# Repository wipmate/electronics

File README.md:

# 📟 Electronics

A collection of small ESP32-powered PCBs for use in smart home appliances.

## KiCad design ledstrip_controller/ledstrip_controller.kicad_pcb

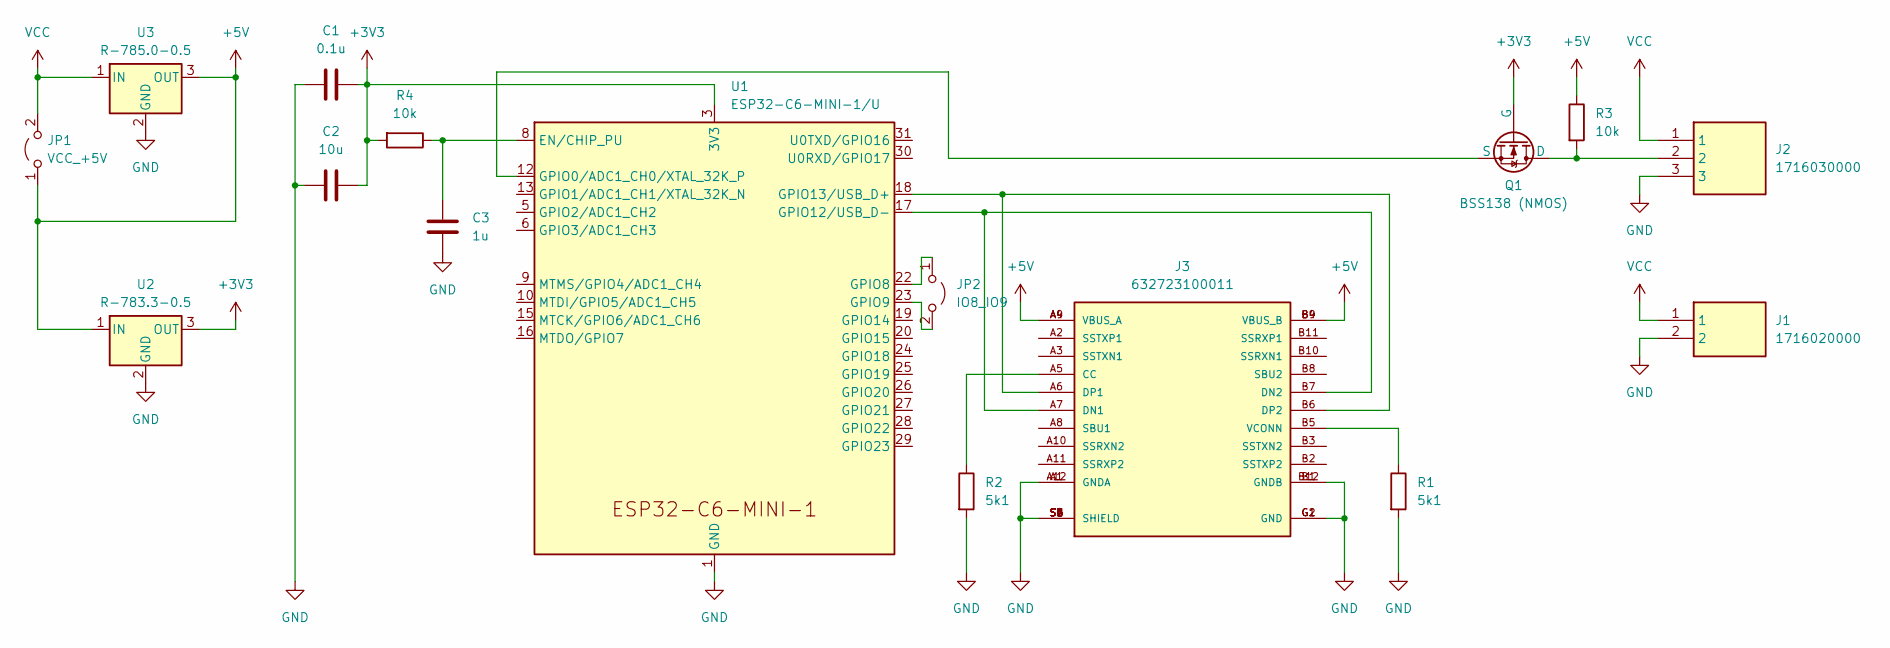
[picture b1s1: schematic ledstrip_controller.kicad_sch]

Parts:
C1: 0.1u; C_0603_1608Metric
C2: 10u; C_0603_1608Metric
C3: 1u; C_0603_1608Metric
J1: 1716020000; Mouser Part Number 470-1716020000
J2: 1716030000; Mouser Part Number 470-1716030000
J3: 632723100011; WURTH_632723100011; PARTREV 001.003
JP1: VCC_+5V; SolderJumper-2_P1.3mm_Open_Pad1.0x1.5mm
JP2: IO8_IO9; SolderJumper-2_P1.3mm_Open_Pad1.0x1.5mm
Q1: BSS138 (NMOS); SOT-23-3
R1, R2: 5k1; R_0603_1608Metric
R3, R4: 10k; R_0603_1608Metric
U1: ESP32-C6-MINI-1/U; ESP32-C6-MINI-1
U2: R-783.3-0.5; Converter_DCDC_RECOM_R-78E-0.5_THT
U3: R-785.0-0.5; Converter_DCDC_RECOM_R-78E-0.5_THT

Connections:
+3V3: C1.2, C2.2, Q1.2 (G), R4.2, U1.3 (3V3), U2.3 (OUT)
+5V: J3.A4 (VBUS_A), J3.A9 (VBUS_A), J3.B4 (VBUS_B), J3.B9 (VBUS_B), JP1.1 (A), R3.1, U2.1 (IN), U3.3 (OUT)
GND: C1.1, C2.1, C3.2, J1.2, J2.3, J3.A1 (GNDA), J3.A12 (GNDA), J3.B1 (GNDB), J3.B12 (GNDB), J3.G1 (GND), J3.G2 (GND), J3.S1 (SHIELD), J3.S2 (SHIELD), J3.S3 (SHIELD), J3.S4 (SHIELD), J3.S5 (SHIELD), J3.S6 (SHIELD), R1.2, R2.2, U1.1 (GND), U1.2 (GND), U1.11 (GND), U1.14 (GND), U1.36 (GND), U1.37 (GND), U1.38 (GND), U1.39 (GND), U1.40 (GND), U1.41 (GND), U1.42 (GND), U1.43 (GND), U1.44 (GND), U1.45 (GND), U1.46 (GND), U1.47 (GND), U1.48 (GND), U1.49 (GND), U1.50 (GND), U1.51 (GND), U1.52 (GND), U1.53 (GND), U2.2 (GND), U3.2 (GND)
unnamed: J3.A5 (CC), R2.1
unnamed: J3.A7 (DN1), J3.B7 (DN2), U1.17 (GPIO12/USB_D-)
unnamed: J3.A6 (DP1), J3.B6 (DP2), U1.18 (GPIO13/USB_D+)
unnamed: J3.B5 (VCONN), R1.1
unnamed: JP2.1 (A), U1.22 (GPIO8)
unnamed: JP2.2 (B), U1.23 (GPIO9)
unnamed: J2.2, Q1.1 (D), R3.2
unnamed: Q1.3 (S), U1.12 (GPIO0/ADC1_CH0/XTAL_32K_P)
unnamed: C3.1, R4.1, U1.8 (EN/CHIP_PU)
VCC: J1.1, J2.1, JP1.2 (B), U3.1 (IN)

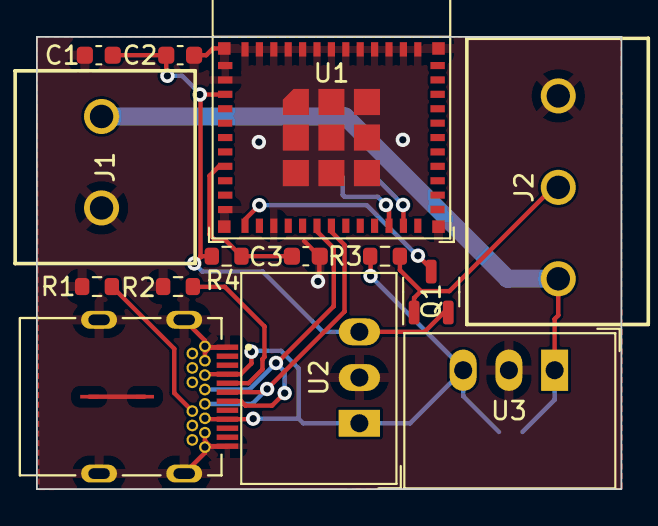
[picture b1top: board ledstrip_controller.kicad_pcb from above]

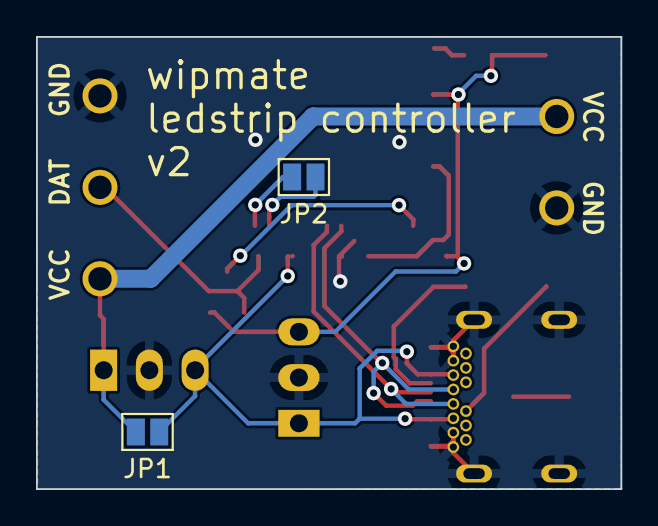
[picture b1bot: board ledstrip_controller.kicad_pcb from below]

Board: 2 copper layers, 32.5 x 25.1 mm, 16 parts (2 on the bottom side), 13 nets.

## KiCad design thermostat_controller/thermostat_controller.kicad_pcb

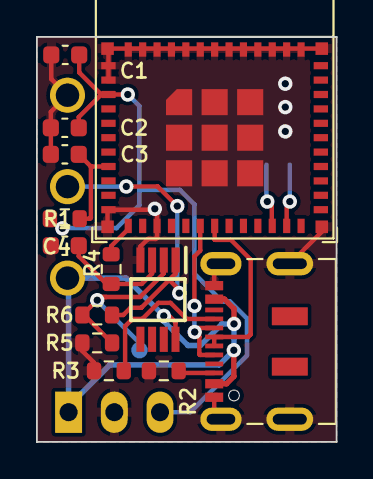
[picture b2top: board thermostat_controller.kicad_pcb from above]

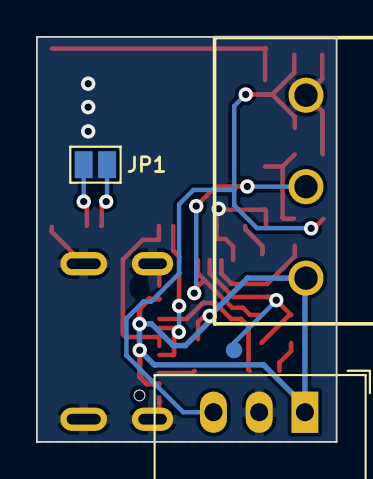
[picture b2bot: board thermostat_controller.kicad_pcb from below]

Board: 2 copper layers, 16.6 x 22.5 mm, 16 parts (3 on the bottom side), 14 nets.

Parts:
C1: 0.1u; C_0603_1608Metric
C2: 10u; C_0603_1608Metric
C3: 1u; C_0603_1608Metric
C4: 2.2u; C_0603_1608Metric
J1: USB_C_Receptacle_USB2.0; USB_C_Receptacle_JAE_DX07S016JA1R1500
J2: 1716030000
JP1: IO8_IO9; SolderJumper-2_P1.3mm_Open_Pad1.0x1.5mm
R1, R4, R5: 10k; R_0603_1608Metric
R2, R3: 5k1; R_0603_1608Metric
R6: 56k; R_0603_1608Metric
U1: R-783.3-0.5; Converter_DCDC_RECOM_R-78E-0.5_THT
U2: ESP32-C6-MINI-1/U; ESP32-C6-MINI-1
U3: LM358; SOP65P490X110-8N

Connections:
+3V3: C1.2, C2.2, R1.2, U1.3 (OUT), U2.3 (3V3)
GND: C1.1, C2.1, C3.2, C4.2, J1.A1 (GND), J1.A12 (GND), J1.B1 (GND), J1.B12 (GND), J1.S1 (SHIELD), J2.3, R2.2, R3.2, R5.2, U1.2 (GND), U2.1 (GND), U2.2 (GND), U2.11 (GND), U2.14 (GND), U2.36 (GND), U2.37 (GND), U2.38 (GND), U2.39 (GND), U2.40 (GND), U2.41 (GND), U2.42 (GND), U2.43 (GND), U2.44 (GND), U2.45 (GND), U2.46 (GND), U2.47 (GND), U2.48 (GND), U2.49 (GND), U2.50 (GND), U2.51 (GND), U2.52 (GND), U2.53 (GND), U3.4 (V-)
unnamed: J1.A5 (CC1), R2.1
unnamed: J1.B5 (CC2), R3.1
unnamed: J2.2, R6.2, U3.1
unnamed: JP1.1 (A), U2.22 (GPIO8)
unnamed: JP1.2 (B), U2.23 (GPIO9)
unnamed: C3.1, R1.1, U2.8 (EN/CHIP_PU)
unnamed: R4.1, U2.12 (GPIO0/ADC1_CH0/XTAL_32K_P)
unnamed: J1.A7 (D-), J1.B7 (D-), U2.17 (GPIO12/USB_D-)
unnamed: J1.A6 (D+), J1.B6 (D+), U2.18 (GPIO13/USB_D+)
unnamed: C4.1, R4.2, U3.3 (+)
unnamed: R5.1, R6.1, U3.2 (-)
VCC: J1.A4 (VBUS), J1.A9 (VBUS), J1.B4 (VBUS), J1.B9 (VBUS), J2.1, U1.1 (IN), U3.8 (V+)

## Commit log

2024-11-25 add README
